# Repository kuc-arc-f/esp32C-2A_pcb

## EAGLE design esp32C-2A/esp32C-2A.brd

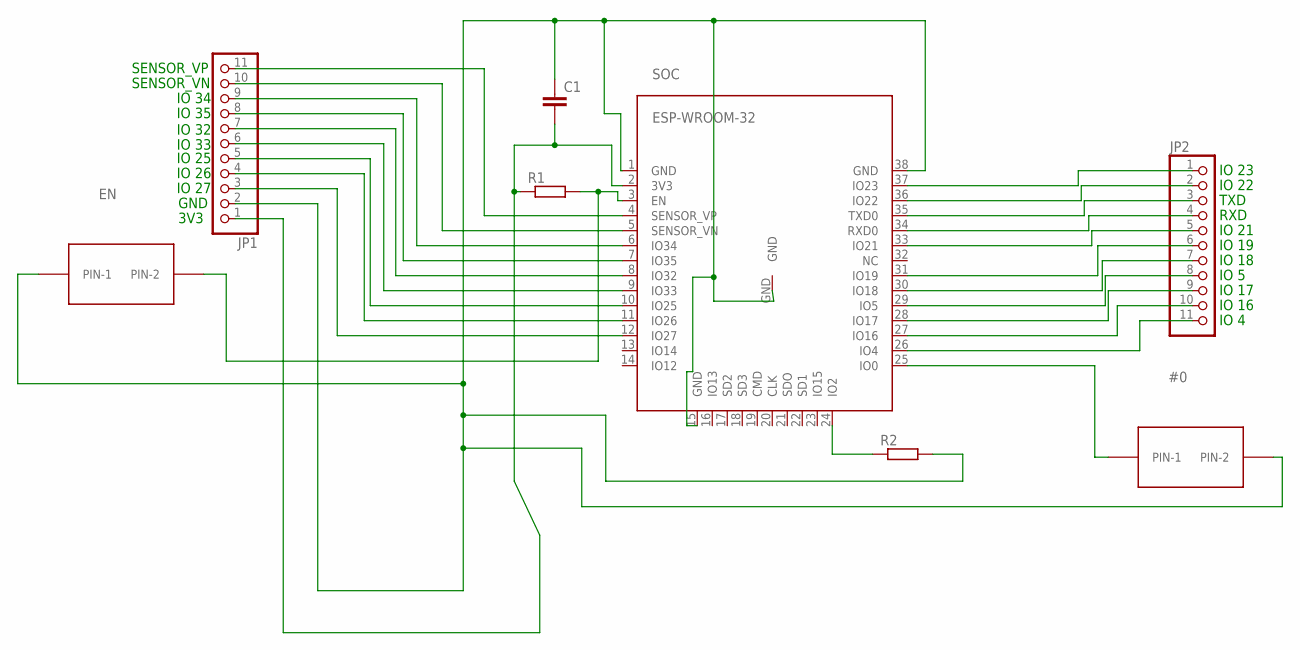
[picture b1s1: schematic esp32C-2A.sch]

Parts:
#0: BTN2-EX; B3F-10XX
C1: C-EUC0603; C0603
EN: BTN2-EX; B3F-10XX
JP1, JP2: PINHD-1X11; 1X11
R1, R2: R-EU_R0603; R0603
SOC: ESP-WROOM-32

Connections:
unnamed: JP2.2, SOC.36 (IO22)
unnamed: #0.1 (PIN-1), SOC.25 (IO0)
unnamed: R2.1, SOC.24 (IO2)
unnamed: JP2.3, SOC.35 (TXD0)
unnamed: JP2.4, SOC.34 (RXD0)
unnamed: JP1.11, SOC.4 (SENSOR_VP)
unnamed: JP2.1, SOC.37 (IO23)
unnamed: EN.2 (PIN-2), R1.2, SOC.3 (EN)
unnamed: JP2.5, SOC.33 (IO21)
unnamed: C1.2, JP1.1, R1.1, SOC.2 (3V3)
unnamed: #0.2 (PIN-2), C1.1, EN.1 (PIN-1), JP1.2, R2.2, SOC.1 (GND), SOC.15 (GND), SOC.38 (GND), SOC.GND
unnamed: JP2.6, SOC.31 (IO19)
unnamed: JP2.7, SOC.30 (IO18)
unnamed: JP2.8, SOC.29 (IO5)
unnamed: JP2.9, SOC.28 (IO17)
unnamed: JP2.10, SOC.27 (IO16)
unnamed: JP2.11, SOC.26 (IO4)
unnamed: JP1.10, SOC.5 (SENSOR_VN)
unnamed: JP1.9, SOC.6 (IO34)
unnamed: JP1.8, SOC.7 (IO35)
unnamed: JP1.7, SOC.8 (IO32)
unnamed: JP1.6, SOC.9 (IO33)
unnamed: JP1.5, SOC.10 (IO25)
unnamed: JP1.4, SOC.11 (IO26)
unnamed: JP1.3, SOC.12 (IO27)

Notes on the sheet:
GND
3V3
SENSOR_VP
SENSOR_VN
IO 27
IO 26
IO 25
IO 33
IO 32
IO 35
IO 34
IO 23
IO 4
IO 16
IO 22
TXD
RXD
IO 21
IO 19
IO 18
IO 5
IO 17

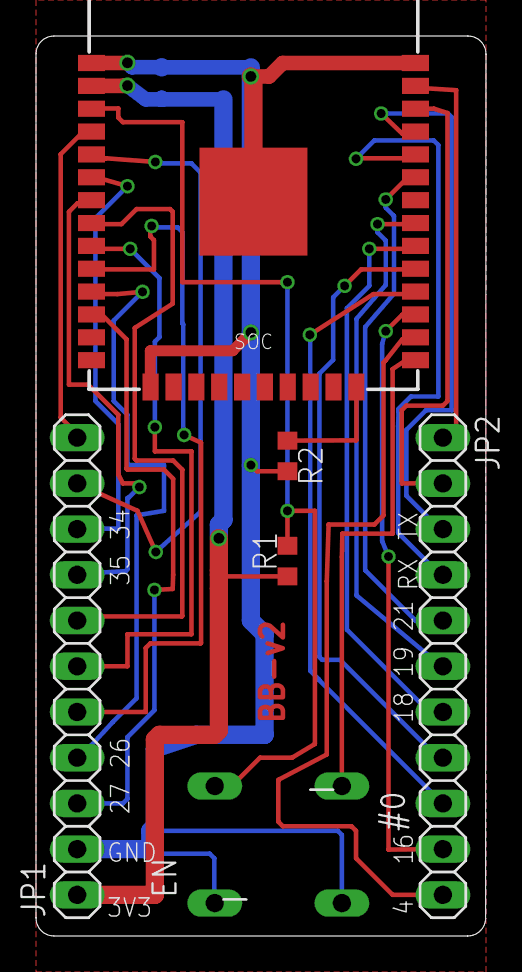
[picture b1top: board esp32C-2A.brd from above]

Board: 2 copper layers, 25.0 x 50.0 mm, 8 parts (1 on the bottom side), 25 nets.

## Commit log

2017-08-20 new, 08-20a2
